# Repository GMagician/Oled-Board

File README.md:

>[!WARNING]
>The transfer of all repositories to my [Codeberg account](https://codeberg.org/GMagician) is currently ongoing. In the future, this project will be continued here!
# SDD1306 1.3" OLED Board

This board has been inspired by Leonerd it's an open source and open hardware.
On the hardware side is fully compatible (not tested with 5V input tolerant boards)
On software side there are some new features usefull for SMuFF device

**PLEASE NOTE REV1 HAS PCB ERRORS. TO PROPERLY WORK NEED SOME PCB, PINS, PADS AND ROUTES CUTTING. THESE SHOULD BE FIXED IN REV2 BRANCH**

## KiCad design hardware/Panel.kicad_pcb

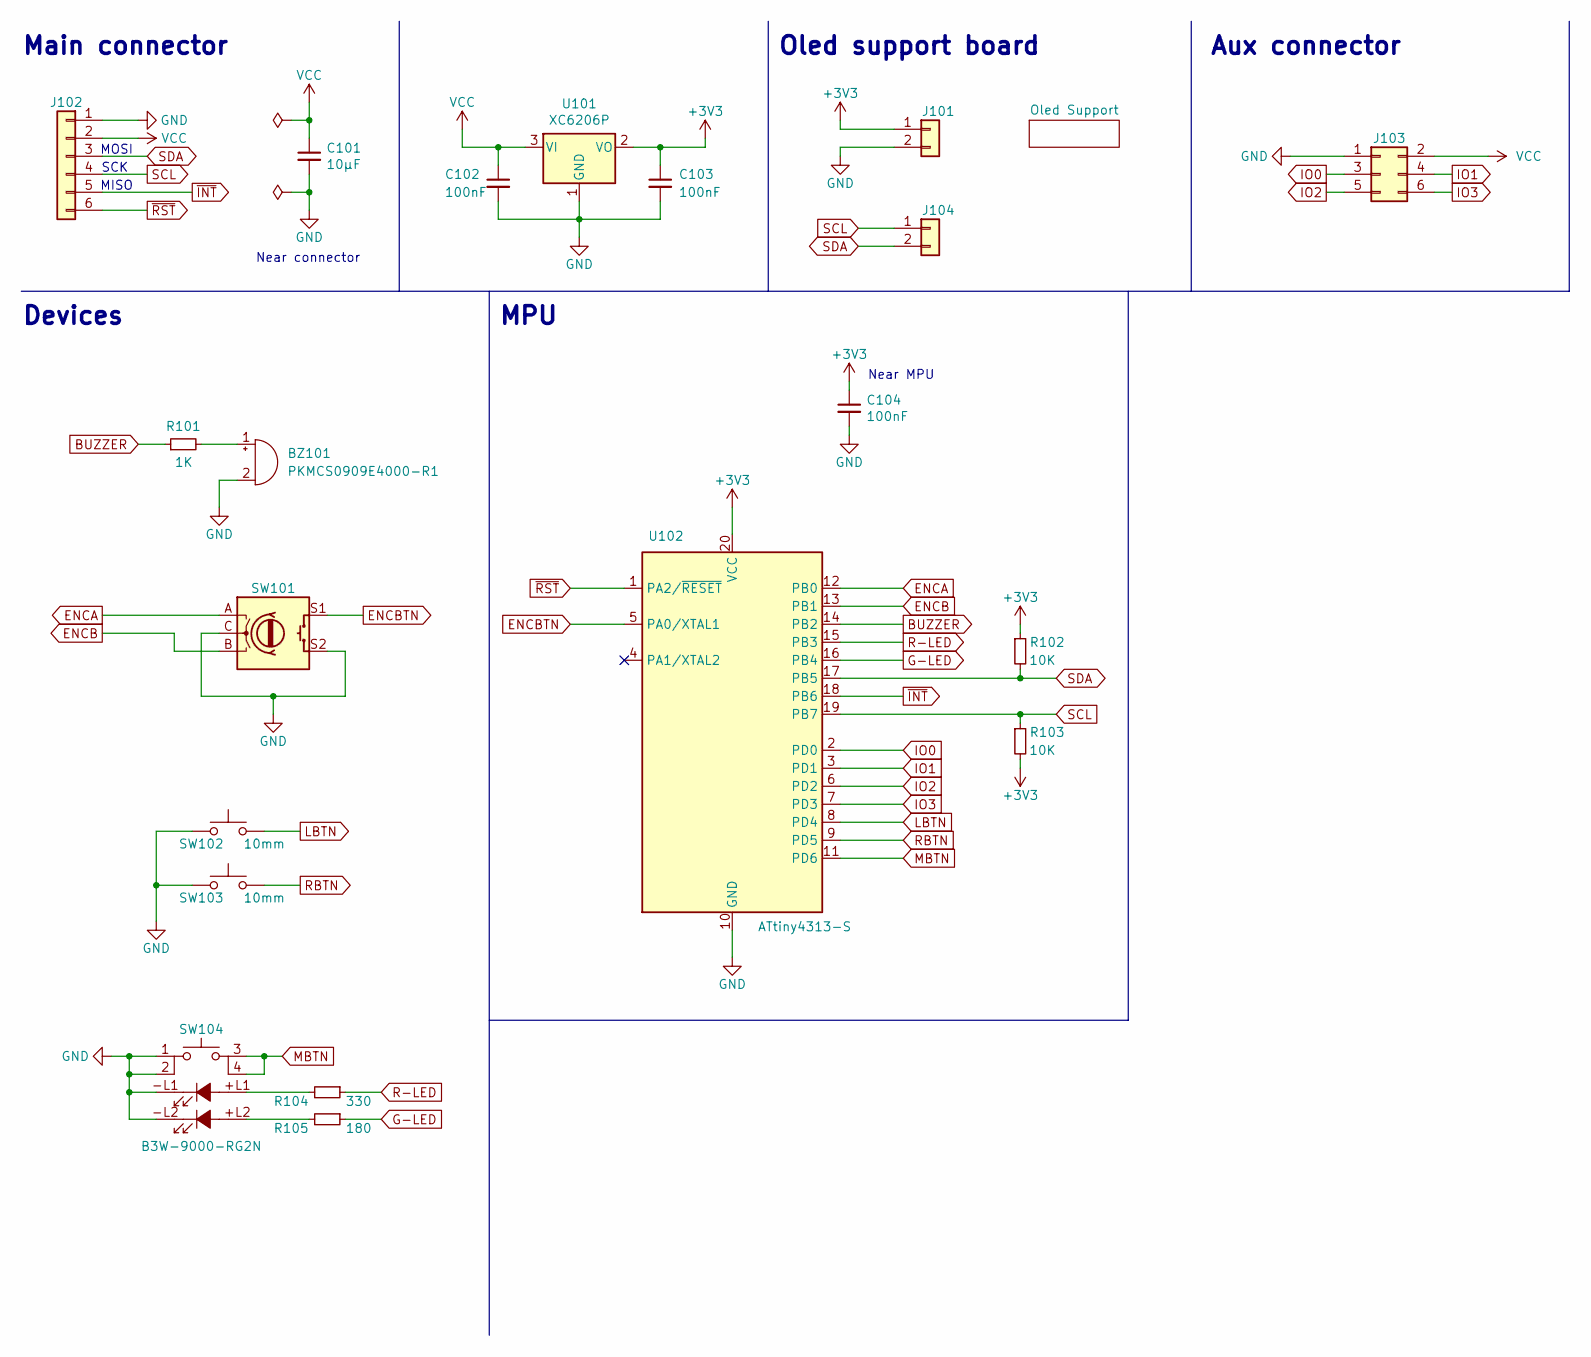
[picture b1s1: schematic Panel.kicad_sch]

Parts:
BZ101: PKMCS0909E4000-R1; Buzzer_Murata_PKMCS0909E
C101: 10µF; C_0805_2012Metric_Pad1.18x1.45mm_HandSolder; LCSC C15850
C102, C103, C104: 100nF; C_0805_2012Metric_Pad1.18x1.45mm_HandSolder; LCSC C49678
J101, J104: Conn_01x02; OledSupport-header
J102: Header; JST_XH_B6B-XH-A_1x06_P2.50mm_Vertical
J103: Header; PinHeader_2x03_P2.54mm_Vertical
R101: 1K; R_0805_2012Metric_Pad1.20x1.40mm_HandSolder; LCSC C17513
R102, R103: 10K; R_0805_2012Metric_Pad1.20x1.40mm_HandSolder; LCSC C17414
R104: 330; R_0805_2012Metric_Pad1.20x1.40mm_HandSolder; LCSC C17630
R105: 180; R_0805_2012Metric_Pad1.20x1.40mm_HandSolder; LCSC C25270
SW101: Rotary Encoder + Switch; RotaryEncoder_Alps_EC11E-Switch_Vertical_H20mm
SW102, SW103: 10mm; SW_SPST_Omron_B3FS-100xP
SW104: B3W-9000-RG2N; B3W-9000-RG2
U101: XC6206P; SOT-23_Handsoldering; LCSC C5446
U102: ATtiny4313-S; SOIC-20W_7.5x12.8mm_P1.27mm

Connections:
+3V3: C103.1, C104.1, J101.1, R102.1, R103.2, U101.2 (VO), U102.20 (VCC); also elsewhere on the board
BUZZER: R101.1, U102.14 (PB2)
ENCA: SW101.A, U102.12 (PB0)
ENCB: SW101.B, U102.13 (PB1)
ENCBTN: SW101.S1, U102.5 (PA0/XTAL1)
G-LED: R105.1, U102.16 (PB4)
GND: BZ101.2 (-), C101.2, C102.2, C103.2, C104.2, J101.2, J102.1, J103.1, SW101.C, SW101.S2, SW102.1, SW103.1, SW104.1, SW104.2, SW104.-L1, SW104.-L2, U101.1 (GND), U102.10 (GND); also elsewhere on the board
IO0: J103.3, U102.2 (PD0)
IO1: J103.4, U102.3 (PD1)
IO2: J103.5, U102.6 (PD2)
IO3: J103.6, U102.7 (PD3)
LBTN: SW102.2, U102.8 (PD4)
MBTN: SW104.3, SW104.4, U102.11 (PD6)
unnamed: BZ101.1 (+), R101.2
unnamed: R104.2, SW104.+L1
unnamed: R105.2, SW104.+L2
R-LED: R104.1, U102.15 (PB3)
RBTN: SW103.2, U102.9 (PD5)
SCL: J102.4, J104.1, R103.1, U102.19 (PB7); also elsewhere on the board
SDA: J102.3, J104.2, R102.2, U102.17 (PB5); also elsewhere on the board
VCC: C101.1, C102.1, J102.2, J103.2, U101.3 (VI)
~INT: J102.5, U102.18 (PB6)
~RST: J102.6, U102.1 (PA2/~RESET)

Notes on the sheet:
SCK
Oled support board
MISO
Main connector
Near MPU
Aux connector
MPU
Devices
MOSI
Near connector

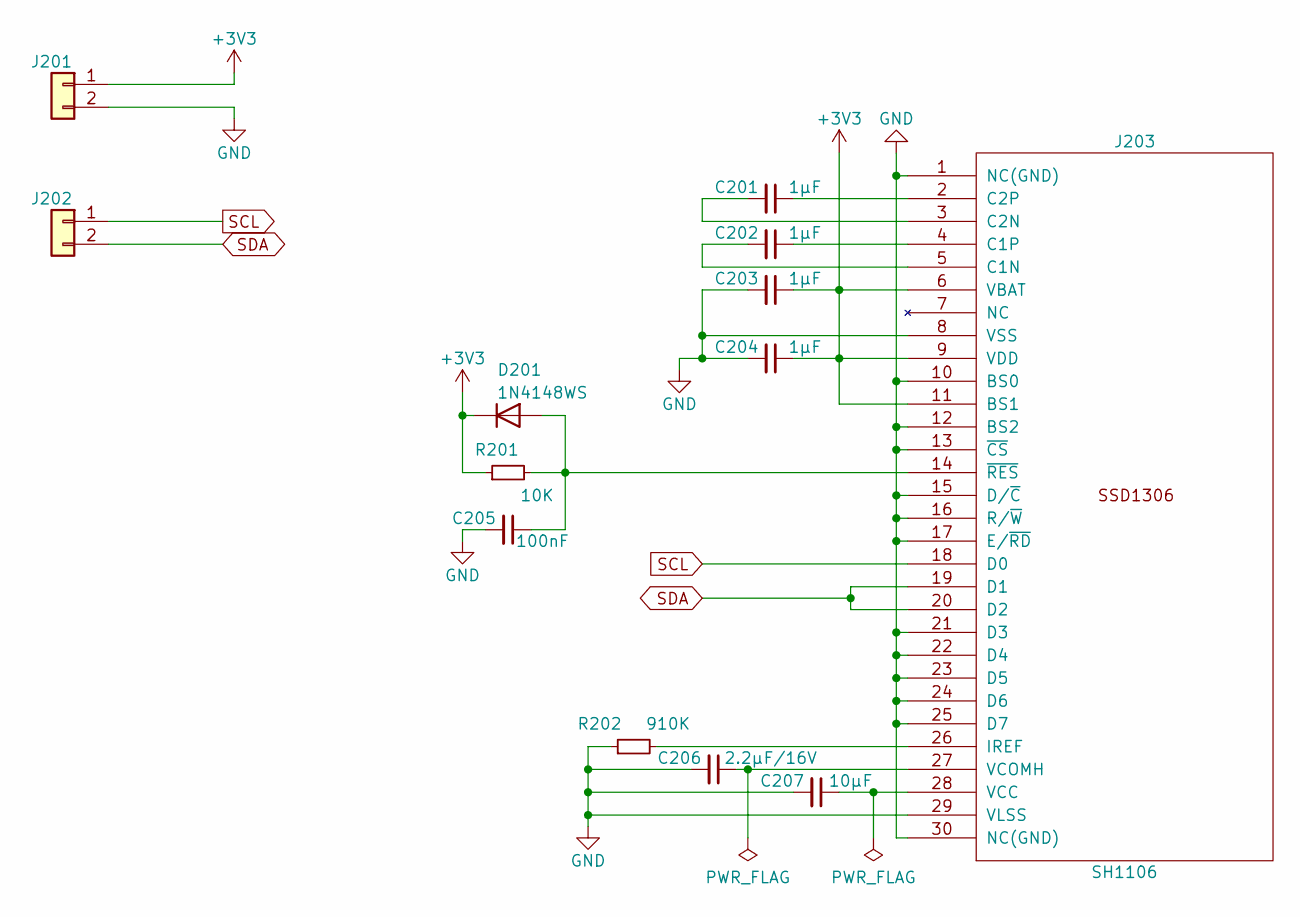
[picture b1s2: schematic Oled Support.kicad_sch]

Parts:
C201, C202, C203, C204: 1µF; C_0805_2012Metric_Pad1.18x1.45mm_HandSolder; LCSC C28323
C205: 100nF; C_0805_2012Metric_Pad1.18x1.45mm_HandSolder; LCSC C49678
C206: 2.2µF/16V; C_0805_2012Metric_Pad1.18x1.45mm_HandSolder; LCSC C49217
C207: 10µF; C_0805_2012Metric_Pad1.18x1.45mm_HandSolder; LCSC C15850
D201: 1N4148WS; D_SOD-323_HandSoldering; LCSC C2128
J201, J202: Conn_01x02; PinHeader_1x02_P2.54mm_Vertical
J203: SH1106; OLED-128O064D
R201: 10K; R_0805_2012Metric_Pad1.20x1.40mm_HandSolder; LCSC C17414
R202: 910K; R_0805_2012Metric_Pad1.20x1.40mm_HandSolder; LCSC C17864

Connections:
+3V3: C203.1, C204.1, D201.1 (K), J201.1, J203.6 (VBAT), J203.9 (VDD), J203.11 (BS1), R201.1; also elsewhere on the board
GND: C203.2, C204.2, C205.2, C206.2, C207.2, J201.2, J203.1 (NC(GND)), J203.8 (VSS), J203.10 (BS0), J203.12 (BS2), J203.13 (~CS), J203.15 (D/~C), J203.16 (R/~W), J203.17 (E/~RD), J203.21 (D3), J203.22 (D4), J203.23 (D5), J203.24 (D6), J203.25 (D7), J203.29 (VLSS), J203.30 (NC(GND)), R202.1; also elsewhere on the board
unnamed: C205.1, D201.2 (A), J203.14 (~RES), R201.2
unnamed: C202.2, J203.5 (C1N)
unnamed: C202.1, J203.4 (C1P)
unnamed: C201.2, J203.3 (C2N)
unnamed: C201.1, J203.2 (C2P)
unnamed: J203.26 (IREF), R202.2
unnamed: C207.1, J203.28 (VCC)
unnamed: C206.1, J203.27 (VCOMH)
SCL: J202.1, J203.18 (D0); also elsewhere on the board
SDA: J202.2, J203.19 (D1), J203.20 (D2); also elsewhere on the board

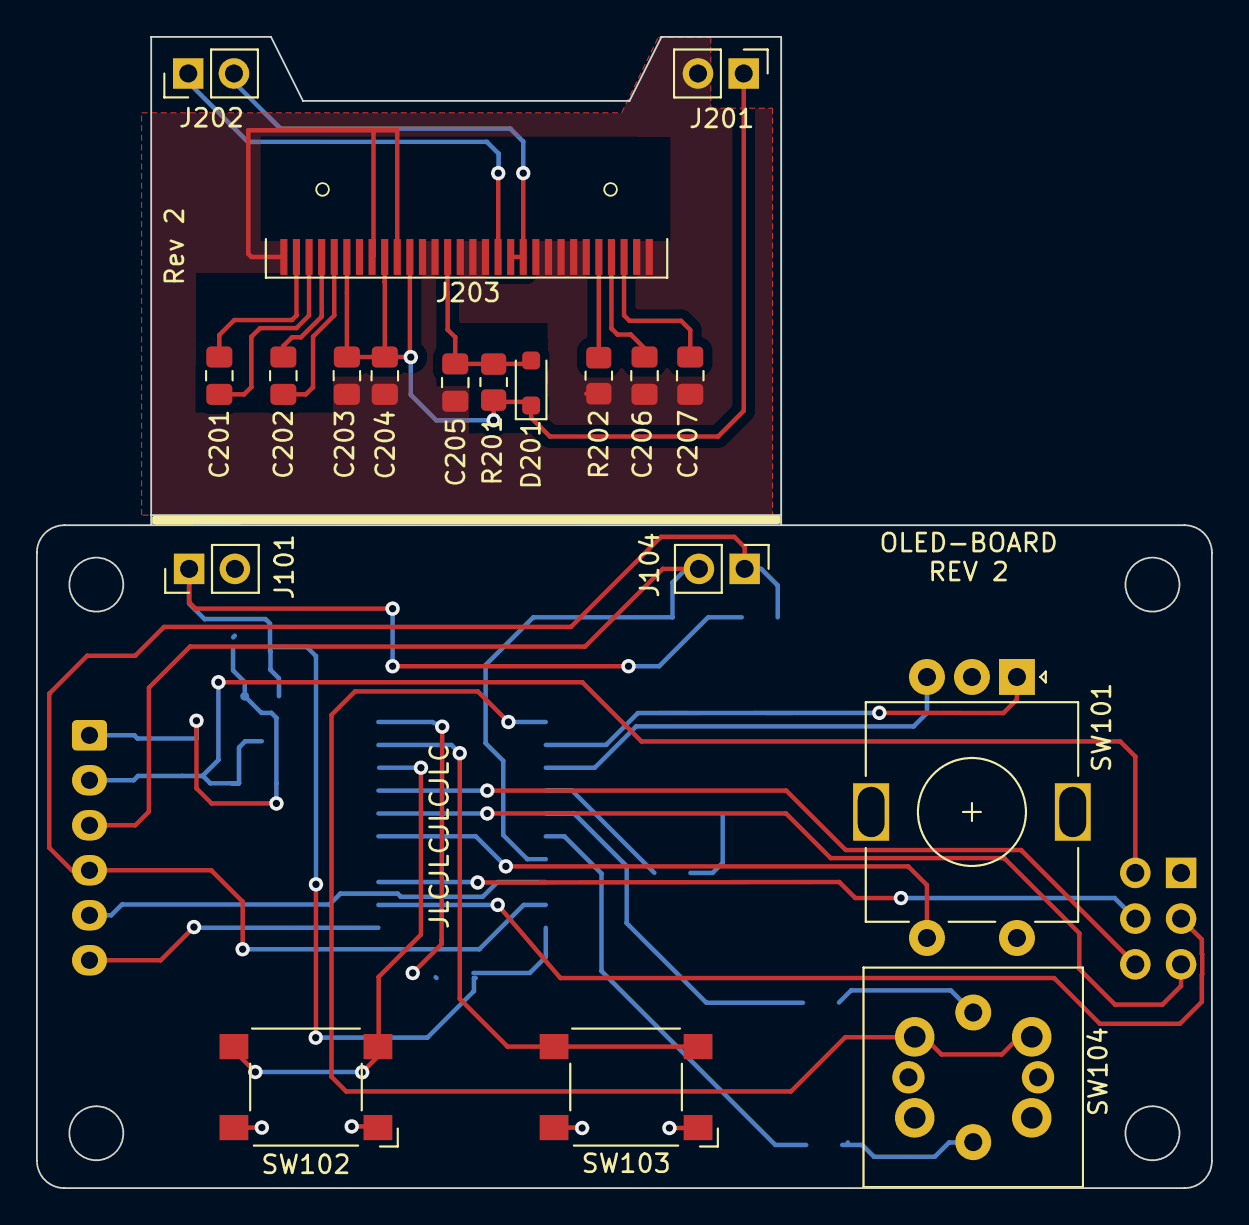
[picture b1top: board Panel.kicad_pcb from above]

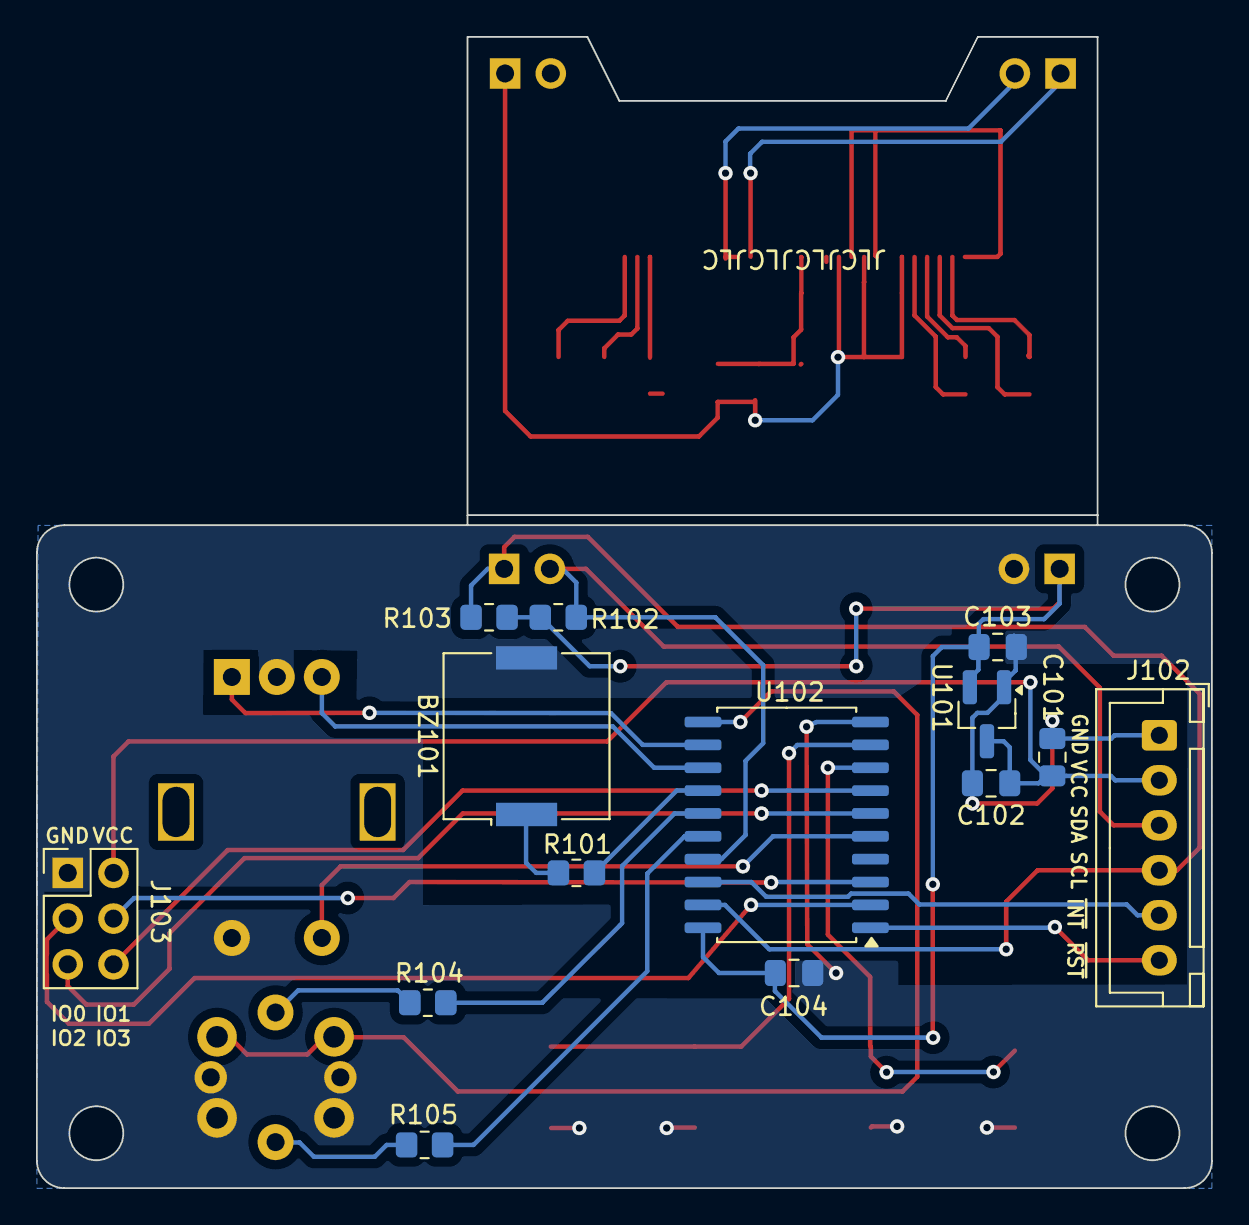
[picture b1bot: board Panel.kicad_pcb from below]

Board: 2 copper layers, 65.3 x 64.0 mm, 33 parts (14 on the bottom side), 31 nets.

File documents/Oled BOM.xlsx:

Supplier | Comment | Quantity
AliExpress | 10µF (805) | 2
AliExpress | 100nF (805) | 4
AliExpress | 1µF (805) | 4
AliExpress | 2.2µF/16V (805) | 1
 | Header (1x6) or JST_XH B6B | 1
AliExpress | Pin Header (1x2) | 2
AliExpress | 1K (805) | 1
AliExpress | 330 (805) | 1
AliExpress | 1N4148WS (SOD323) | 1
AliExpress | 180 (805) | 1
AliExpress | 10K (805) | 3
AliExpress | 910K (805) | 1
AliExpress | SH1106 (1.3”) | 1
AliExpress | Rotary Encoder (Half-15mm) | 1
AliExpress | Switches (6x6x10mm) | 2
AliExpress | XC6206P (662K SOT-23) | 1
RS Components | B3W-9000-RG2N | 1
RS Components | ATtiny4313 (SOIC-20W) | 1
RS Components | Buzzer (PKMCS0909E4000-R1) | 1
JLCPCB | PCB | 1

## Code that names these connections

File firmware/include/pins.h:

#pragma once

#define ENCBTN_PIN            PA0
#define UNUSED1_PIN           PA1
//#define RESET_PIN           PA2

#define ENCA_PIN              PB0
#define ENCB_PIN              PB1
#define BUZZER_PIN            PB2
#define REDLED_PIN            PB3
#define GREENLED_PIN          PB4
//#define SDA_PIN             PB5
#define INTERRUPT_PIN         PB6
//#define SCL_PIN             PB7

#define GPIO0_PIN             PD0
#define GPIO1_PIN             PD1
#define GPIO2_PIN             PD2
#define GPIO3_PIN             PD3
#define LEFTBTN_PIN           PD4
#define RIGHTBTN_PIN          PD5
#define MAINBTN_PIN           PD6

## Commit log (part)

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2021-01-01 Fix eeprom default programming
2021-01-03 Add datasheet
2021-02-08 Report PCB issues
2021-02-20 Add PCB cut to warnings
    Oled pins are too far from edge and requires a PCB cut (sand) to be soldered
2021-03-30 Fixed wheel direction event
    Now event report proper cw/ccw action
2021-03-31 Added pdf datasheet
2021-03-31 Moved oled pads
    Moved oled pins by 2mm (they where too far from edge and were impossible to solder)
2021-03-31 Rev2 fixes
    - Move I2C pullups on main board
    - Fix left/right/main buttons traces
2021-03-31 Some GND plane changes
2021-03-31 BOM added
2021-04-01 SH1106 name fix
2023-08-08 KiCad 7.0 update
2023-12-29 Remove unused file
2024-01-19 Minor changes
2024-03-17 Update to Kicad 8
